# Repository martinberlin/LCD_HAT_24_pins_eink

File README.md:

LCD_HAT with 24 pin SPI Eink circuit<br>
-----------------------------------

Copyright (c) 2023 BitBank Software, Inc.<br>
bitbank@pobox.com<br>
<br>
Collaboration to make the SPI Eink port by [Fasani Corp](https://fasani.de)

A simple PCB to easily connect LCD breakout boards to Arduino Nano or Feather MCU boards. Includes 2 momentary push buttons and Qwiic I2C connector. The GPIOs used for the LCD connection are marked next to the female header. Likewise the buttons.
<br>
This photo shows an Arduino Nano RP2040 Connect and UnexpectedMaker FeatherS3 both using the same board and 2 types of LCDs supported with this pinout:
<br>
<br>

<br>

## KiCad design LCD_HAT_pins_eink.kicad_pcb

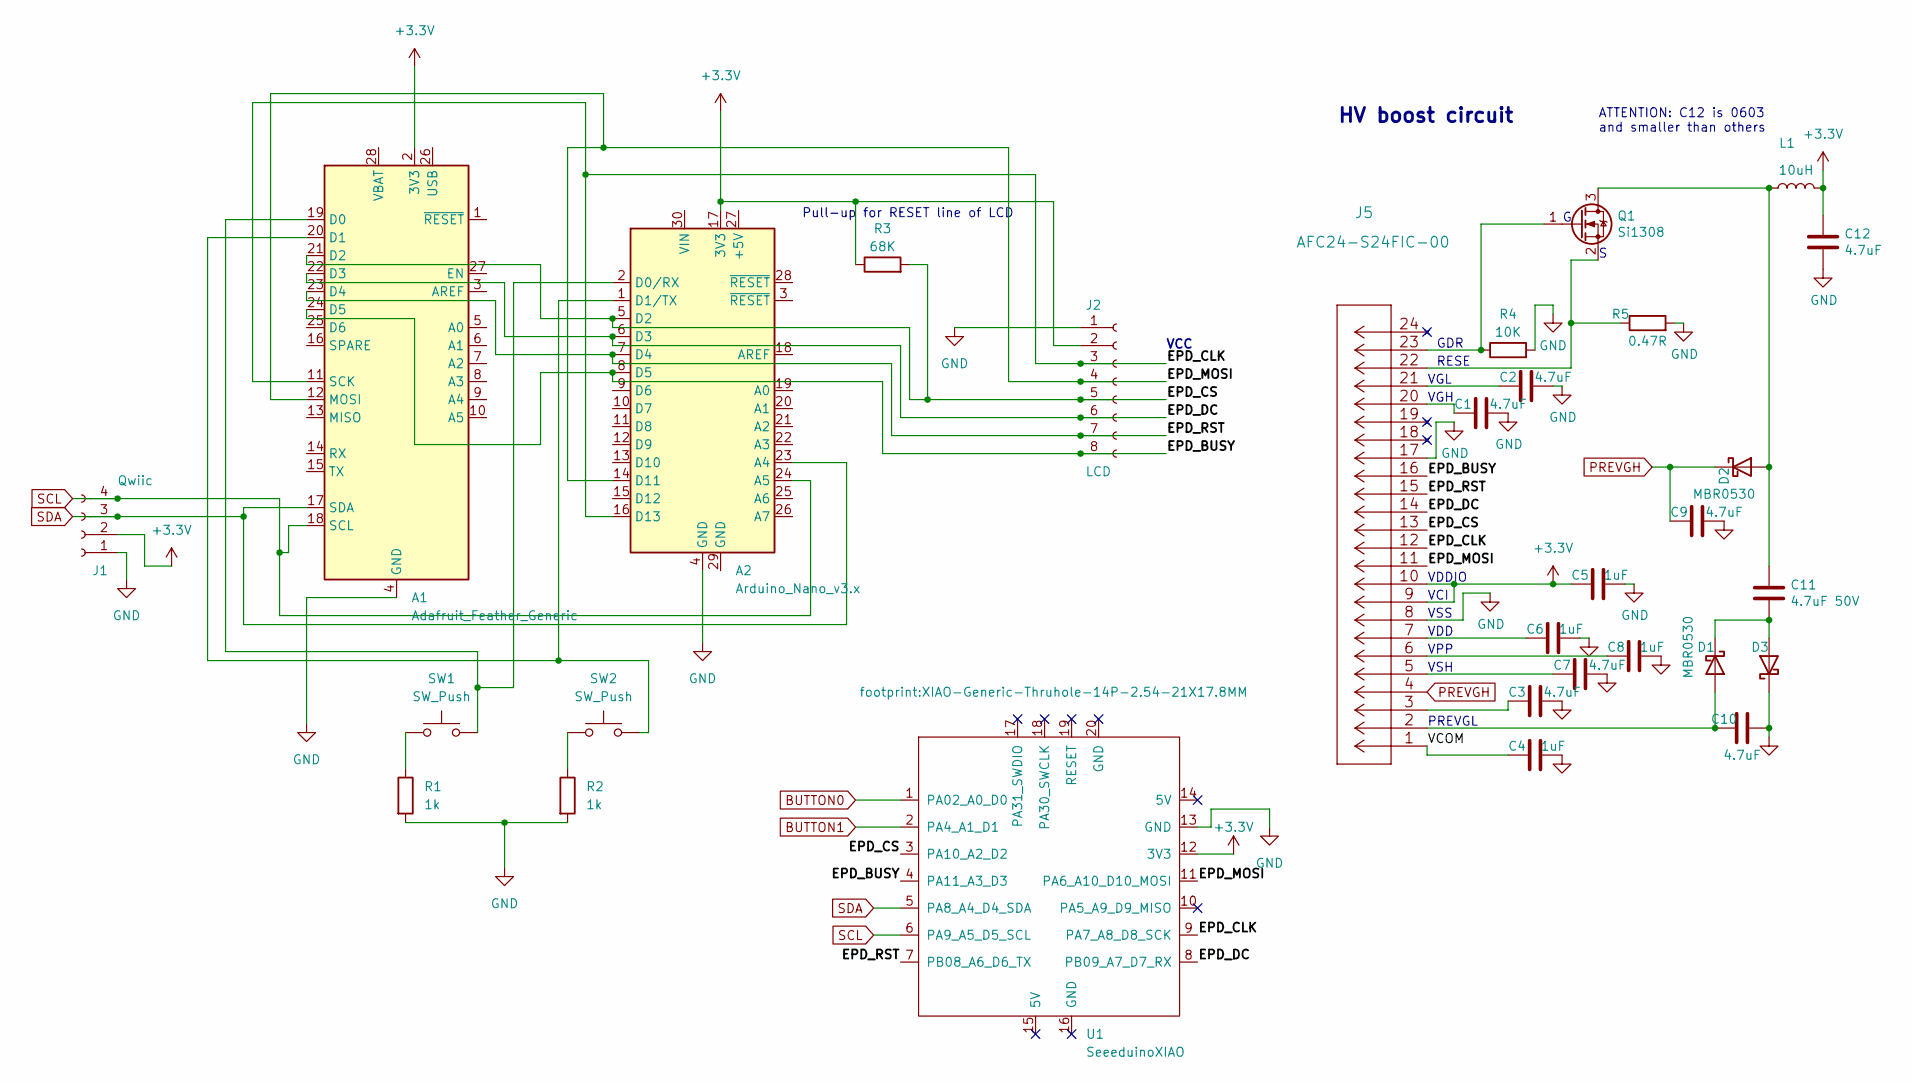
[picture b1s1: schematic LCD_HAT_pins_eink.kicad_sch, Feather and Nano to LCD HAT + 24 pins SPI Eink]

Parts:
A1: Adafruit_Feather_Generic; Adafruit_Feather
A2: Arduino_Nano_v3.x; Arduino_Nano
C1, C2, C3, C7, C9, C10: 4.7uF; C_0805_2012Metric_Pad1.18x1.45mm_HandSolder; LCSC C1779
C4, C5, C6, C8: 1uF; C_0805_2012Metric_Pad1.18x1.45mm_HandSolder; LCSC C28323
C11: 4.7uF 50V; C_0805_2012Metric_Pad1.18x1.45mm_HandSolder; LCSC C1779
C12: 4.7uF; C_0603_1608Metric; LCSC C19666
D1, D2, D3: MBR0530; D_SOD-123; LCSC C77336
J1: Qwiic; QWIIC_SM04B-SRSS-TB_LFSN_; LCSC C160404
J2: LCD; PinSocket_1x08_P2.54mm_Vertical
J5: AFC24-S24FIC-00; LCSC C262292
L1: 10uH; SWPA4030S1R0NT; LCSC C38117
Q1: Si1308; SOT-323_SC-70; LCSC C469327
R1, R2: 1k; R_0603_1608Metric; LCSC C11702
R3: 68K; R_0603_1608Metric; LCSC C245058
R4: 10K; R_0603_1608Metric; LCSC C25804
R5: 0.47R; R_0603_1608Metric; LCSC C103895
SW1, SW2: SW_Push; SW_Push_1P1T_NO_Vertical_Wuerth_434133025816; LCSC C19190908
U1: SeeeduinoXIAO; XIAO-Generic-Thruhole-14P-2.54-21X17.8MM

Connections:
+3.3V: A1.2 (3V3), A2.17 (3V3), C5.2, C12.2, J1.2, J2.2, J5.9, J5.10, L1.2, R3.1, U1.12 (3V3)
/EPD_BUSY: A1.24 (D5), A2.8 (D5), J2.8, J5.16, U1.4 (PA11_A3_D3)
/EPD_CLK: A1.11 (SCK), A2.16 (D13), J2.3, J5.12, U1.9 (PA7_A8_D8_SCK)
/EPD_CS: A1.21 (D2), A2.5 (D2), J2.5, J5.13, R3.2, U1.3 (PA10_A2_D2)
/EPD_DC: A1.22 (D3), A2.6 (D3), J2.6, J5.14, U1.8 (PB09_A7_D7_RX)
/EPD_MOSI: A1.12 (MOSI), A2.14 (D11), J2.4, J5.11, U1.11 (PA6_A10_D10_MOSI)
/EPD_RST: A1.23 (D4), A2.7 (D4), J2.7, J5.15, U1.7 (PB08_A6_D6_TX)
/VCOM: C4.2, J5.1
BUTTON0: U1.1 (PA02_A0_D0)
BUTTON1: U1.2 (PA4_A1_D1)
GND: A1.4 (GND), A2.4 (GND), C1.1, C2.1, C3.1, C4.1, C5.1, C6.1, C7.1, C8.1, C9.1, C10.1, C12.1, D3.1 (K), J1.1, J2.1, J5.8, J5.17, R1.2, R2.2, R4.2, R5.2, U1.13 (GND)
unnamed: A1.19 (D0), A2.2 (D0/RX), SW1.2
unnamed: A1.20 (D1), A2.1 (D1/TX), SW2.2
unnamed: C1.2, J5.20
unnamed: C2.2, J5.21
unnamed: C3.2, J5.3
unnamed: C6.2, J5.7
unnamed: C7.2, J5.5
unnamed: C8.2, J5.6
unnamed: C10.2, D1.2 (A), J5.2
unnamed: C11.1, D1.1 (K), D3.2 (A)
unnamed: C11.2, D2.2 (A), L1.1, Q1.3 (D)
unnamed: J5.23, Q1.1 (G), R4.1
unnamed: J5.22, Q1.2 (S), R5.1
unnamed: R1.1, SW1.1
unnamed: R2.1, SW2.1
PREVGH: C9.2, D2.1 (K), J5.4
SCL: A1.18 (SCL), A2.24 (A5), J1.4, U1.6 (PA9_A5_D5_SCL)
SDA: A1.17 (SDA), A2.23 (A4), J1.3, U1.5 (PA8_A4_D4_SDA)

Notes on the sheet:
PREVGL
VGH
ATTENTION: C12 is 0603 and smaller than others
VSS
VDD
RESE
VGL
Pull-up for RESET line of LCD
GDR
VCI
VCC
HV boost circuit
VDDIO
VPP
VSH

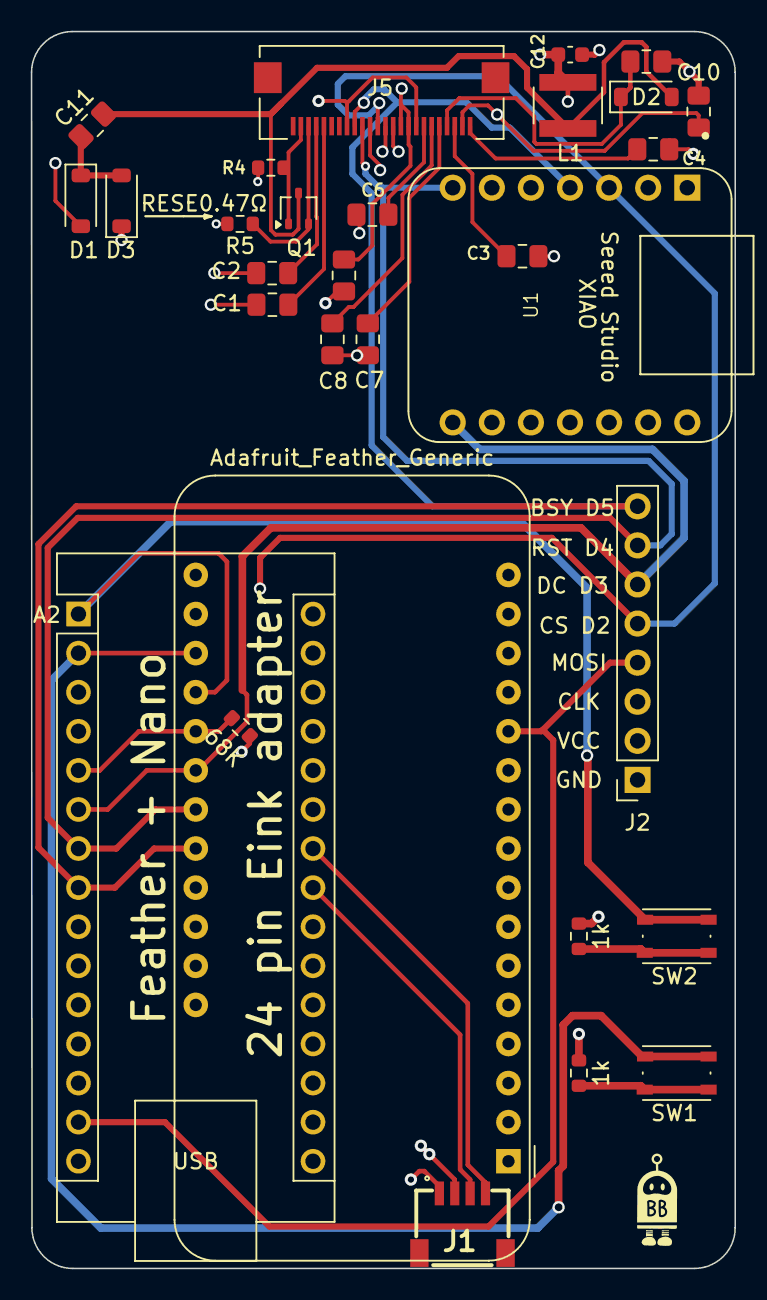
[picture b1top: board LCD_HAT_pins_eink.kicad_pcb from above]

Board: 4 copper layers, 45.7 x 80.4 mm, 30 parts (0 on the bottom side), 27 nets.

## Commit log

2025-09-30 Rework routing
2025-10-02 Update readme with images
2025-10-03 FAB Files 1.0
2025-10-26 FIX pin not connected to GND in 24 pin FPC

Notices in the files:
parts and their libraries:
Copyright 2021 Accelerated Designs. All rights reserved.
